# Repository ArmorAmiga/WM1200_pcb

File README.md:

# ArmorAmiga "Wishmaster" PCB repository

This is an early prototype of ARM-based A1200 turbo board.

PCB design was created in [KiCAD EDA](https://kicad.org/).

It consists of the following parts:
 * Wishmaster carrier board
 * Alinx AC7010/AC7020 Xilinx Zynq development board (available on Aliexpress, for example: https://aliexpress.ru/item/4000585279066.html). Most likely, you will also need a Xilinx JTAG cable to work with it as a developer.

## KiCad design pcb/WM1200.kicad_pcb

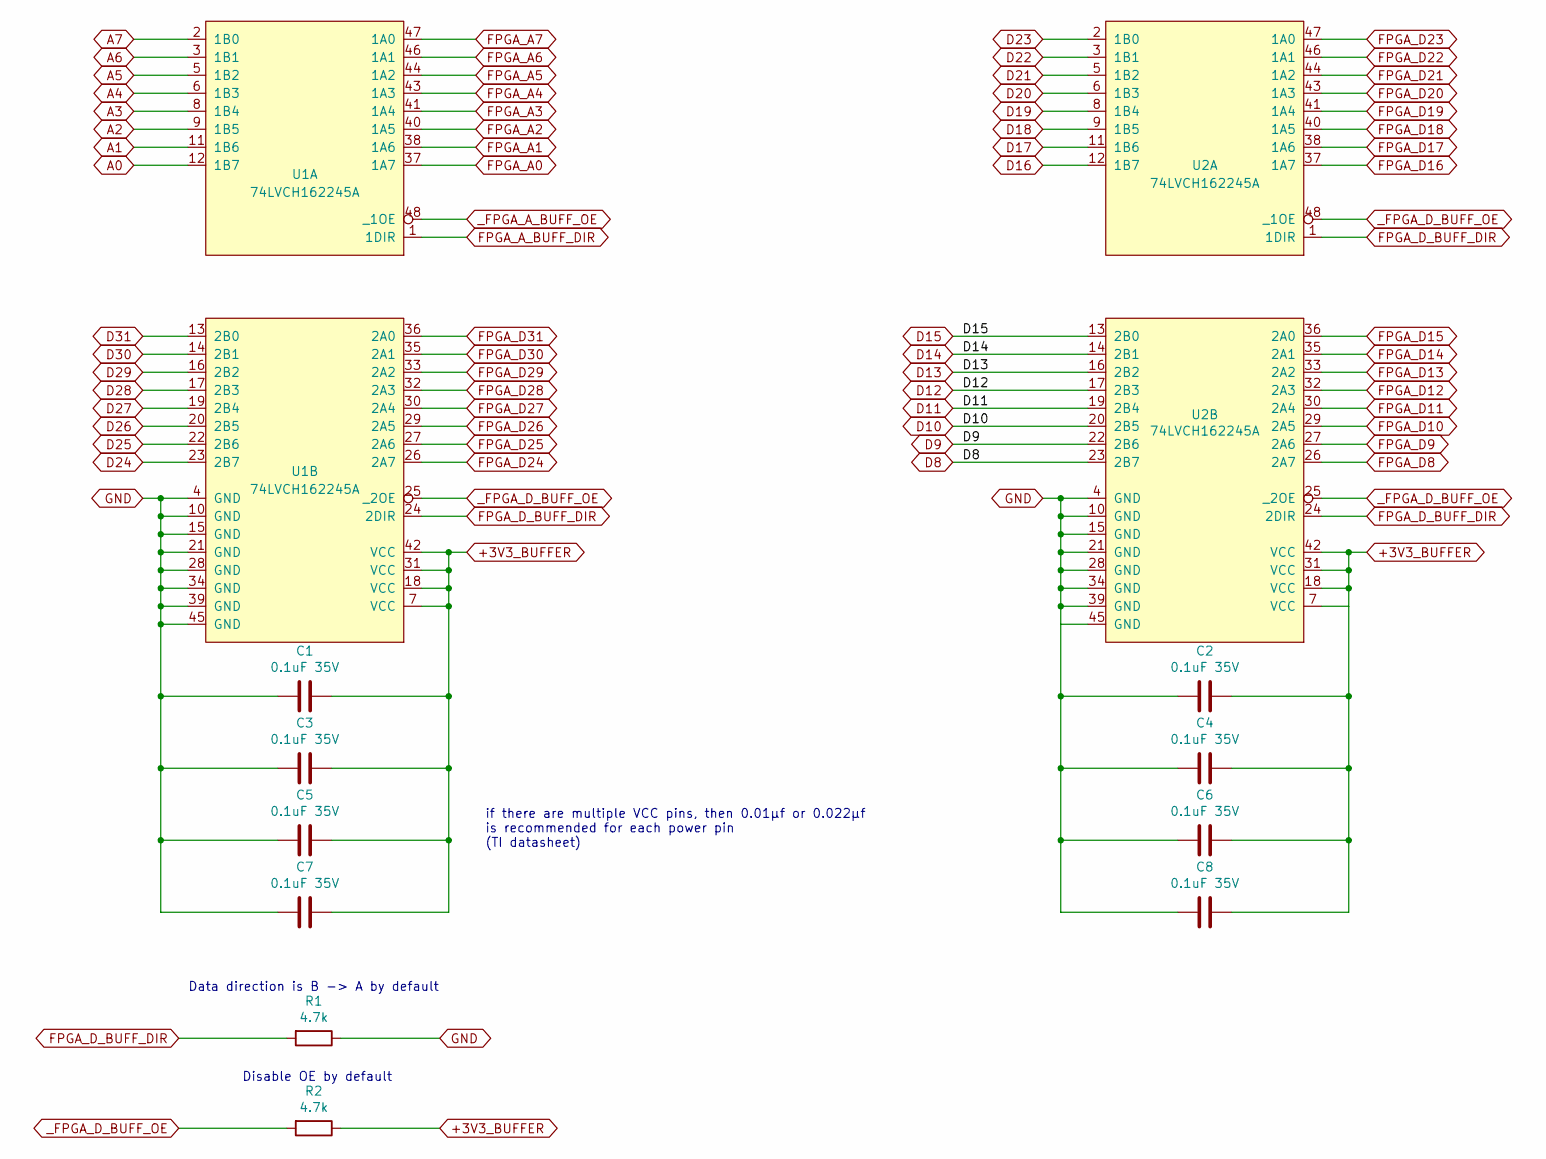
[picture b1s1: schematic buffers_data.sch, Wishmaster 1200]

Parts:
C1, C2, C3, C4, C5, C6, C7, C8: 0.1uF 35V; C_0402_1005Metric
R1, R2: 4.7k; R_0603_1608Metric_Pad1.05x0.95mm_HandSolder
U1, U2: 74LVCH162245A; TSSOP-48_6.1x12.5mm_P0.5mm

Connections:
+3V3_BUFFER: C1.2, C2.2, C3.2, C4.2, C5.2, C6.2, C7.2, C8.2, R2.1, U1.7 (VCC), U1.18 (VCC), U1.31 (VCC), U1.42 (VCC), U2.7 (VCC), U2.18 (VCC), U2.31 (VCC), U2.42 (VCC); also elsewhere on the board
A0: U1.12 (1B7); also elsewhere on the board
A1: U1.11 (1B6); also elsewhere on the board
A2: U1.9 (1B5); also elsewhere on the board
A3: U1.8 (1B4); also elsewhere on the board
A4: U1.6 (1B3); also elsewhere on the board
A5: U1.5 (1B2); also elsewhere on the board
A6: U1.3 (1B1); also elsewhere on the board
A7: U1.2 (1B0); also elsewhere on the board
D8: U2.23 (2B7); also elsewhere on the board
D9: U2.22 (2B6); also elsewhere on the board
D10: U2.20 (2B5); also elsewhere on the board
D11: U2.19 (2B4); also elsewhere on the board
D12: U2.17 (2B3); also elsewhere on the board
D13: U2.16 (2B2); also elsewhere on the board
D14: U2.14 (2B1); also elsewhere on the board
D15: U2.13 (2B0); also elsewhere on the board
D16: U2.12 (1B7); also elsewhere on the board
D17: U2.11 (1B6); also elsewhere on the board
D18: U2.9 (1B5); also elsewhere on the board
D19: U2.8 (1B4); also elsewhere on the board
D20: U2.6 (1B3); also elsewhere on the board
D21: U2.5 (1B2); also elsewhere on the board
D22: U2.3 (1B1); also elsewhere on the board
D23: U2.2 (1B0); also elsewhere on the board
D24: U1.23 (2B7); also elsewhere on the board
D25: U1.22 (2B6); also elsewhere on the board
D26: U1.20 (2B5); also elsewhere on the board
D27: U1.19 (2B4); also elsewhere on the board
D28: U1.17 (2B3); also elsewhere on the board
D29: U1.16 (2B2); also elsewhere on the board
D30: U1.14 (2B1); also elsewhere on the board
D31: U1.13 (2B0); also elsewhere on the board
FPGA_A0: U1.37 (1A7); also elsewhere on the board
FPGA_A1: U1.38 (1A6); also elsewhere on the board
FPGA_A2: U1.40 (1A5); also elsewhere on the board
FPGA_A3: U1.41 (1A4); also elsewhere on the board
FPGA_A4: U1.43 (1A3); also elsewhere on the board
FPGA_A5: U1.44 (1A2); also elsewhere on the board
FPGA_A6: U1.46 (1A1); also elsewhere on the board
FPGA_A7: U1.47 (1A0); also elsewhere on the board
FPGA_A_BUFF_DIR: U1.1 (1DIR); also elsewhere on the board
FPGA_D8: U2.26 (2A7); also elsewhere on the board
FPGA_D9: U2.27 (2A6); also elsewhere on the board
FPGA_D10: U2.29 (2A5); also elsewhere on the board
FPGA_D11: U2.30 (2A4); also elsewhere on the board
FPGA_D12: U2.32 (2A3); also elsewhere on the board
FPGA_D13: U2.33 (2A2); also elsewhere on the board
FPGA_D14: U2.35 (2A1); also elsewhere on the board
FPGA_D15: U2.36 (2A0); also elsewhere on the board
FPGA_D16: U2.37 (1A7); also elsewhere on the board
FPGA_D17: U2.38 (1A6); also elsewhere on the board
FPGA_D18: U2.40 (1A5); also elsewhere on the board
FPGA_D19: U2.41 (1A4); also elsewhere on the board
FPGA_D20: U2.43 (1A3); also elsewhere on the board
FPGA_D21: U2.44 (1A2); also elsewhere on the board
FPGA_D22: U2.46 (1A1); also elsewhere on the board
FPGA_D23: U2.47 (1A0); also elsewhere on the board
FPGA_D24: U1.26 (2A7); also elsewhere on the board
FPGA_D25: U1.27 (2A6); also elsewhere on the board
FPGA_D26: U1.29 (2A5); also elsewhere on the board
FPGA_D27: U1.30 (2A4); also elsewhere on the board
FPGA_D28: U1.32 (2A3); also elsewhere on the board
FPGA_D29: U1.33 (2A2); also elsewhere on the board
FPGA_D30: U1.35 (2A1); also elsewhere on the board
FPGA_D31: U1.36 (2A0); also elsewhere on the board
FPGA_D_BUFF_DIR: R1.2, U1.24 (2DIR), U2.1 (1DIR), U2.24 (2DIR); also elsewhere on the board
GND: C1.1, C2.1, C3.1, C4.1, C5.1, C6.1, C7.1, C8.1, R1.1, U1.4 (GND), U1.10 (GND), U1.15 (GND), U1.21 (GND), U1.28 (GND), U1.34 (GND), U1.39 (GND), U1.45 (GND), U2.4 (GND), U2.10 (GND), U2.15 (GND), U2.21 (GND), U2.28 (GND), U2.34 (GND), U2.39 (GND), U2.45 (GND); also elsewhere on the board
_FPGA_A_BUFF_OE: U1.48 (_1OE); also elsewhere on the board
_FPGA_D_BUFF_OE: R2.2, U1.25 (_2OE), U2.25 (_2OE), U2.48 (_1OE); also elsewhere on the board

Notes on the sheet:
Disable OE by default
Data direction is B -> A by default
if there are multiple VCC pins, then 0.01μf or 0.022μf is recommended for each power pin (TI datasheet)

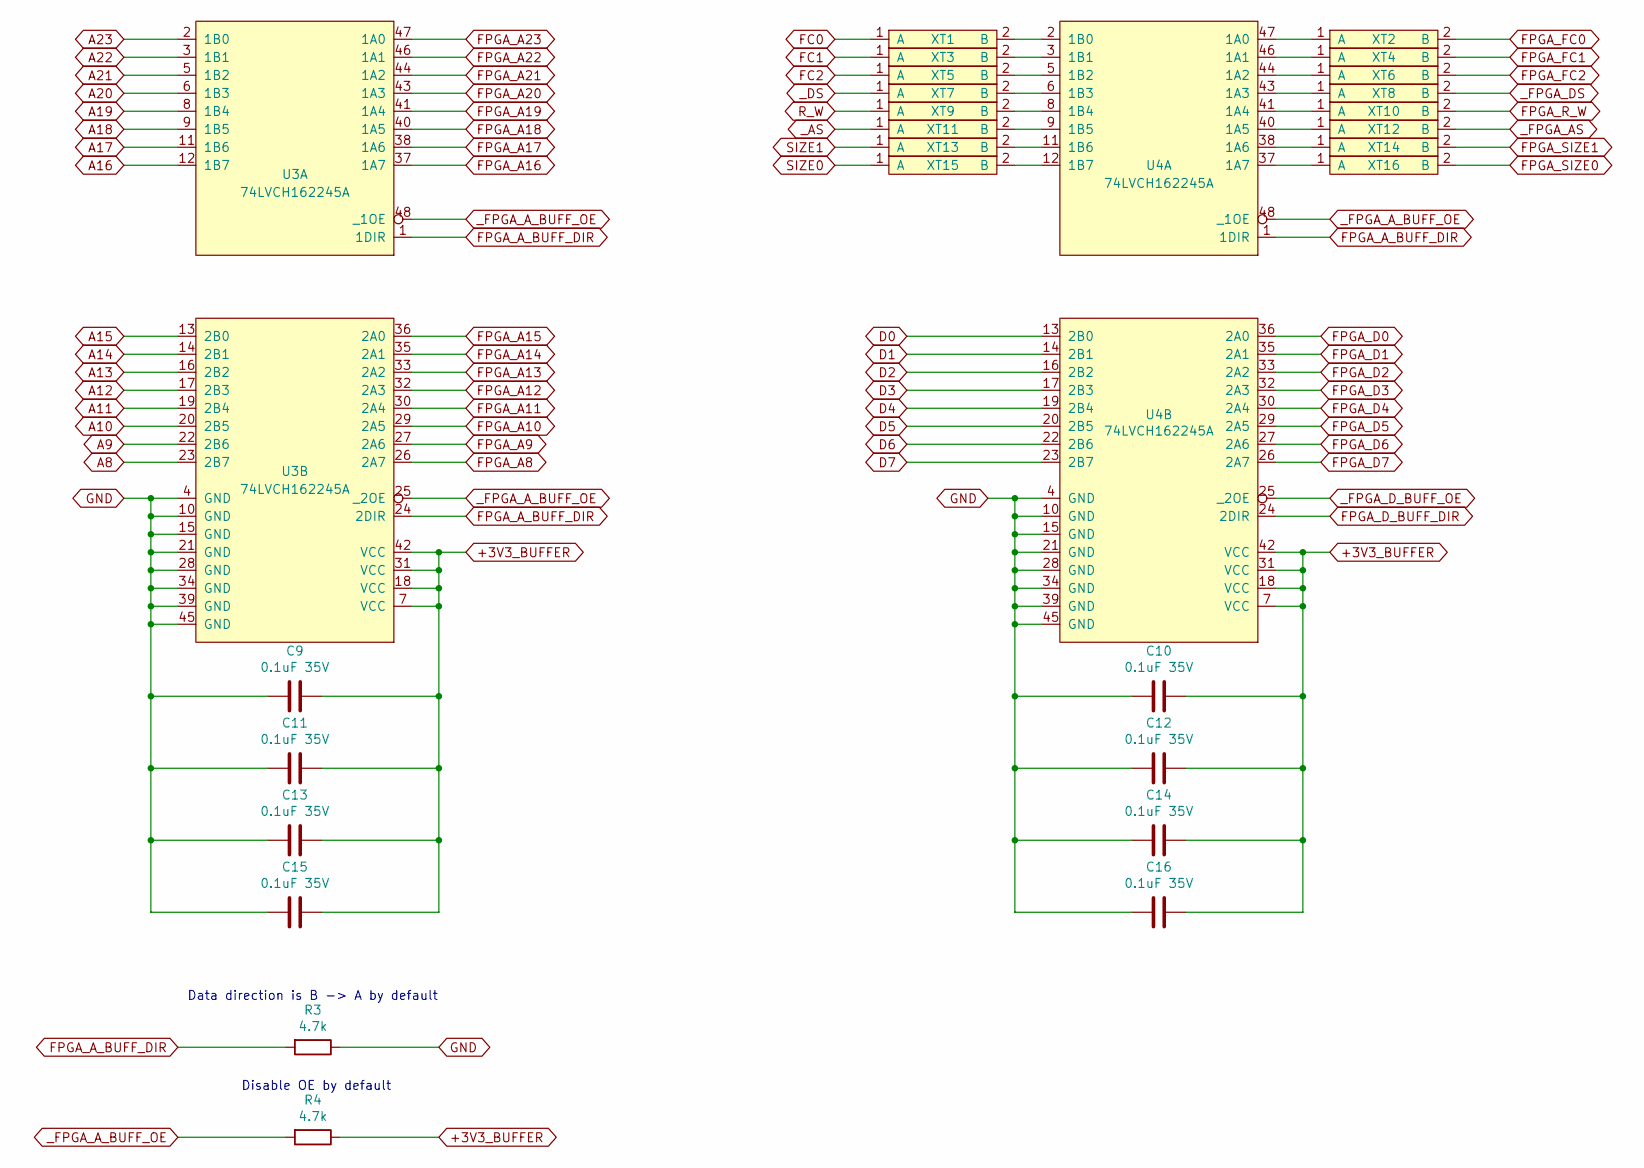
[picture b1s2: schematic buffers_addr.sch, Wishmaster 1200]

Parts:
C9, C10, C11, C12, C13, C14, C15, C16: 0.1uF 35V; C_0402_1005Metric
R3, R4: 4.7k; R_0603_1608Metric_Pad1.05x0.95mm_HandSolder
U3, U4: 74LVCH162245A; TSSOP-48_6.1x12.5mm_P0.5mm
XT1, XT2, XT3, XT4, XT5, XT6, XT7, XT8, XT9, XT10, XT11, XT12, XT13, XT14, XT15, XT16: testpoint_cutline

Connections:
+3V3_BUFFER: C9.2, C10.2, C11.2, C12.2, C13.2, C14.2, C15.2, C16.2, R4.1, U3.7 (VCC), U3.18 (VCC), U3.31 (VCC), U3.42 (VCC), U4.7 (VCC), U4.18 (VCC), U4.31 (VCC), U4.42 (VCC); also elsewhere on the board
A8: U3.23 (2B7); also elsewhere on the board
A9: U3.22 (2B6); also elsewhere on the board
A10: U3.20 (2B5); also elsewhere on the board
A11: U3.19 (2B4); also elsewhere on the board
A12: U3.17 (2B3); also elsewhere on the board
A13: U3.16 (2B2); also elsewhere on the board
A14: U3.14 (2B1); also elsewhere on the board
A15: U3.13 (2B0); also elsewhere on the board
A16: U3.12 (1B7); also elsewhere on the board
A17: U3.11 (1B6); also elsewhere on the board
A18: U3.9 (1B5); also elsewhere on the board
A19: U3.8 (1B4); also elsewhere on the board
A20: U3.6 (1B3); also elsewhere on the board
A21: U3.5 (1B2); also elsewhere on the board
A22: U3.3 (1B1); also elsewhere on the board
A23: U3.2 (1B0); also elsewhere on the board
D0: U4.13 (2B0); also elsewhere on the board
D1: U4.14 (2B1); also elsewhere on the board
D2: U4.16 (2B2); also elsewhere on the board
D3: U4.17 (2B3); also elsewhere on the board
D4: U4.19 (2B4); also elsewhere on the board
D5: U4.20 (2B5); also elsewhere on the board
D6: U4.22 (2B6); also elsewhere on the board
D7: U4.23 (2B7); also elsewhere on the board
FC0: XT1.1 (A); also elsewhere on the board
FC1: XT3.1 (A); also elsewhere on the board
FC2: XT5.1 (A); also elsewhere on the board
FPGA_A8: U3.26 (2A7); also elsewhere on the board
FPGA_A9: U3.27 (2A6); also elsewhere on the board
FPGA_A10: U3.29 (2A5); also elsewhere on the board
FPGA_A11: U3.30 (2A4); also elsewhere on the board
FPGA_A12: U3.32 (2A3); also elsewhere on the board
FPGA_A13: U3.33 (2A2); also elsewhere on the board
FPGA_A14: U3.35 (2A1); also elsewhere on the board
FPGA_A15: U3.36 (2A0); also elsewhere on the board
FPGA_A16: U3.37 (1A7); also elsewhere on the board
FPGA_A17: U3.38 (1A6); also elsewhere on the board
FPGA_A18: U3.40 (1A5); also elsewhere on the board
FPGA_A19: U3.41 (1A4); also elsewhere on the board
FPGA_A20: U3.43 (1A3); also elsewhere on the board
FPGA_A21: U3.44 (1A2); also elsewhere on the board
FPGA_A22: U3.46 (1A1); also elsewhere on the board
FPGA_A23: U3.47 (1A0); also elsewhere on the board
FPGA_A_BUFF_DIR: R3.2, U3.1 (1DIR), U3.24 (2DIR), U4.1 (1DIR); also elsewhere on the board
FPGA_D0: U4.36 (2A0); also elsewhere on the board
FPGA_D1: U4.35 (2A1); also elsewhere on the board
FPGA_D2: U4.33 (2A2); also elsewhere on the board
FPGA_D3: U4.32 (2A3); also elsewhere on the board
FPGA_D4: U4.30 (2A4); also elsewhere on the board
FPGA_D5: U4.29 (2A5); also elsewhere on the board
FPGA_D6: U4.27 (2A6); also elsewhere on the board
FPGA_D7: U4.26 (2A7); also elsewhere on the board
FPGA_D_BUFF_DIR: U4.24 (2DIR); also elsewhere on the board
FPGA_FC0: XT2.2 (B); also elsewhere on the board
FPGA_FC1: XT4.2 (B); also elsewhere on the board
FPGA_FC2: XT6.2 (B); also elsewhere on the board
FPGA_R_W: XT10.2 (B); also elsewhere on the board
FPGA_SIZE0: XT16.2 (B); also elsewhere on the board
FPGA_SIZE1: XT14.2 (B); also elsewhere on the board
GND: C9.1, C10.1, C11.1, C12.1, C13.1, C14.1, C15.1, C16.1, R3.1, U3.4 (GND), U3.10 (GND), U3.15 (GND), U3.21 (GND), U3.28 (GND), U3.34 (GND), U3.39 (GND), U3.45 (GND), U4.4 (GND), U4.10 (GND), U4.15 (GND), U4.21 (GND), U4.28 (GND), U4.34 (GND), U4.39 (GND), U4.45 (GND); also elsewhere on the board
unnamed: U4.2 (1B0), XT1.2 (B)
unnamed: U4.3 (1B1), XT3.2 (B)
unnamed: U4.5 (1B2), XT5.2 (B)
unnamed: U4.6 (1B3), XT7.2 (B)
unnamed: U4.8 (1B4), XT9.2 (B)
unnamed: U4.9 (1B5), XT11.2 (B)
unnamed: U4.11 (1B6), XT13.2 (B)
unnamed: U4.12 (1B7), XT15.2 (B)
unnamed: U4.37 (1A7), XT16.1 (A)
unnamed: U4.38 (1A6), XT14.1 (A)
unnamed: U4.40 (1A5), XT12.1 (A)
unnamed: U4.41 (1A4), XT10.1 (A)
unnamed: U4.43 (1A3), XT8.1 (A)
unnamed: U4.44 (1A2), XT6.1 (A)
unnamed: U4.46 (1A1), XT4.1 (A)
unnamed: U4.47 (1A0), XT2.1 (A)
R_W: XT9.1 (A); also elsewhere on the board
SIZE0: XT15.1 (A); also elsewhere on the board
SIZE1: XT13.1 (A); also elsewhere on the board
_AS: XT11.1 (A); also elsewhere on the board
_DS: XT7.1 (A); also elsewhere on the board
_FPGA_AS: XT12.2 (B); also elsewhere on the board
_FPGA_A_BUFF_OE: R4.2, U3.25 (_2OE), U3.48 (_1OE), U4.48 (_1OE); also elsewhere on the board
_FPGA_DS: XT8.2 (B); also elsewhere on the board
_FPGA_D_BUFF_OE: U4.25 (_2OE); also elsewhere on the board

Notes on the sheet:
Disable OE by default
Data direction is B -> A by default

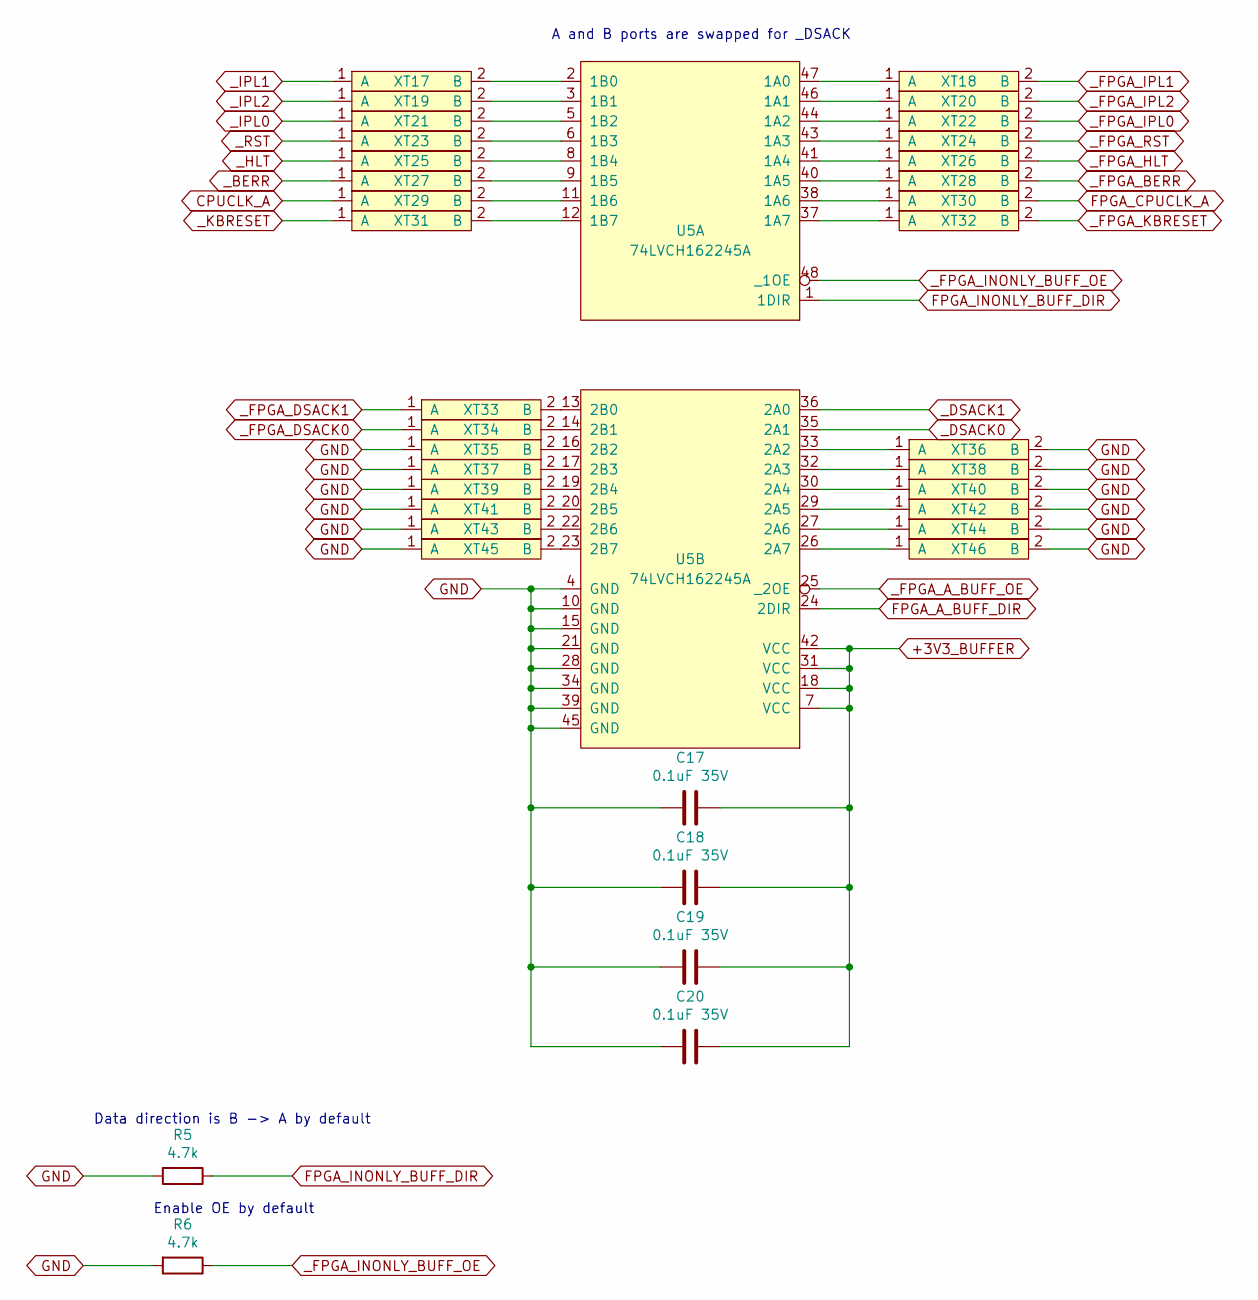
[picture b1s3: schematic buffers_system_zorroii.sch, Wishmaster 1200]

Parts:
C17, C18, C19, C20: 0.1uF 35V; C_0402_1005Metric
R5, R6: 4.7k; R_0603_1608Metric_Pad1.05x0.95mm_HandSolder
U5: 74LVCH162245A; TSSOP-48_6.1x12.5mm_P0.5mm
XT17, XT18, XT19, XT20, XT21, XT22, XT23, XT24, XT25, XT26, XT27, XT28, XT29, XT30, XT31, XT32, XT33, XT34, XT35, XT36, XT37, XT38, XT39, XT40, XT41, XT42, XT43, XT44, XT45, XT46: testpoint_cutline

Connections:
+3V3_BUFFER: C17.2, C18.2, C19.2, C20.2, U5.7 (VCC), U5.18 (VCC), U5.31 (VCC), U5.42 (VCC); also elsewhere on the board
CPUCLK_A: XT29.1 (A); also elsewhere on the board
FPGA_A_BUFF_DIR: U5.24 (2DIR); also elsewhere on the board
FPGA_CPUCLK_A: XT30.2 (B); also elsewhere on the board
FPGA_INONLY_BUFF_DIR: R5.1, U5.1 (1DIR)
GND: C17.1, C18.1, C19.1, C20.1, R5.2, R6.2, U5.4 (GND), U5.10 (GND), U5.15 (GND), U5.21 (GND), U5.28 (GND), U5.34 (GND), U5.39 (GND), U5.45 (GND), XT35.1 (A), XT36.2 (B), XT37.1 (A), XT38.2 (B), XT39.1 (A), XT40.2 (B), XT41.1 (A), XT42.2 (B), XT43.1 (A), XT44.2 (B), XT45.1 (A), XT46.2 (B); also elsewhere on the board
unnamed: U5.2 (1B0), XT17.2 (B)
unnamed: U5.3 (1B1), XT19.2 (B)
unnamed: U5.5 (1B2), XT21.2 (B)
unnamed: U5.6 (1B3), XT23.2 (B)
unnamed: U5.8 (1B4), XT25.2 (B)
unnamed: U5.9 (1B5), XT27.2 (B)
unnamed: U5.11 (1B6), XT29.2 (B)
unnamed: U5.12 (1B7), XT31.2 (B)
unnamed: U5.13 (2B0), XT33.2 (B)
unnamed: U5.14 (2B1), XT34.2 (B)
unnamed: U5.16 (2B2), XT35.2 (B)
unnamed: U5.17 (2B3), XT37.2 (B)
unnamed: U5.19 (2B4), XT39.2 (B)
unnamed: U5.20 (2B5), XT41.2 (B)
unnamed: U5.22 (2B6), XT43.2 (B)
unnamed: U5.23 (2B7), XT45.2 (B)
unnamed: U5.26 (2A7), XT46.1 (A)
unnamed: U5.27 (2A6), XT44.1 (A)
unnamed: U5.29 (2A5), XT42.1 (A)
unnamed: U5.30 (2A4), XT40.1 (A)
unnamed: U5.32 (2A3), XT38.1 (A)
unnamed: U5.33 (2A2), XT36.1 (A)
unnamed: U5.37 (1A7), XT32.1 (A)
unnamed: U5.38 (1A6), XT30.1 (A)
unnamed: U5.40 (1A5), XT28.1 (A)
unnamed: U5.41 (1A4), XT26.1 (A)
unnamed: U5.43 (1A3), XT24.1 (A)
unnamed: U5.44 (1A2), XT22.1 (A)
unnamed: U5.46 (1A1), XT20.1 (A)
unnamed: U5.47 (1A0), XT18.1 (A)
_BERR: XT27.1 (A); also elsewhere on the board
_DSACK0: U5.35 (2A1); also elsewhere on the board
_DSACK1: U5.36 (2A0); also elsewhere on the board
_FPGA_A_BUFF_OE: U5.25 (_2OE); also elsewhere on the board
_FPGA_BERR: XT28.2 (B); also elsewhere on the board
_FPGA_DSACK0: XT34.1 (A); also elsewhere on the board
_FPGA_DSACK1: XT33.1 (A); also elsewhere on the board
_FPGA_HLT: XT26.2 (B); also elsewhere on the board
_FPGA_INONLY_BUFF_OE: R6.1, U5.48 (_1OE)
_FPGA_IPL0: XT22.2 (B); also elsewhere on the board
_FPGA_IPL1: XT18.2 (B); also elsewhere on the board
_FPGA_IPL2: XT20.2 (B); also elsewhere on the board
_FPGA_KBRESET: XT32.2 (B); also elsewhere on the board
_FPGA_RST: XT24.2 (B); also elsewhere on the board
_HLT: XT25.1 (A); also elsewhere on the board
_IPL0: XT21.1 (A); also elsewhere on the board
_IPL1: XT17.1 (A); also elsewhere on the board
_IPL2: XT19.1 (A); also elsewhere on the board
_KBRESET: XT31.1 (A); also elsewhere on the board
_RST: XT23.1 (A); also elsewhere on the board

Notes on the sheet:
Enable OE by default
Data direction is B -> A by default
A and B ports are swapped for _DSACK

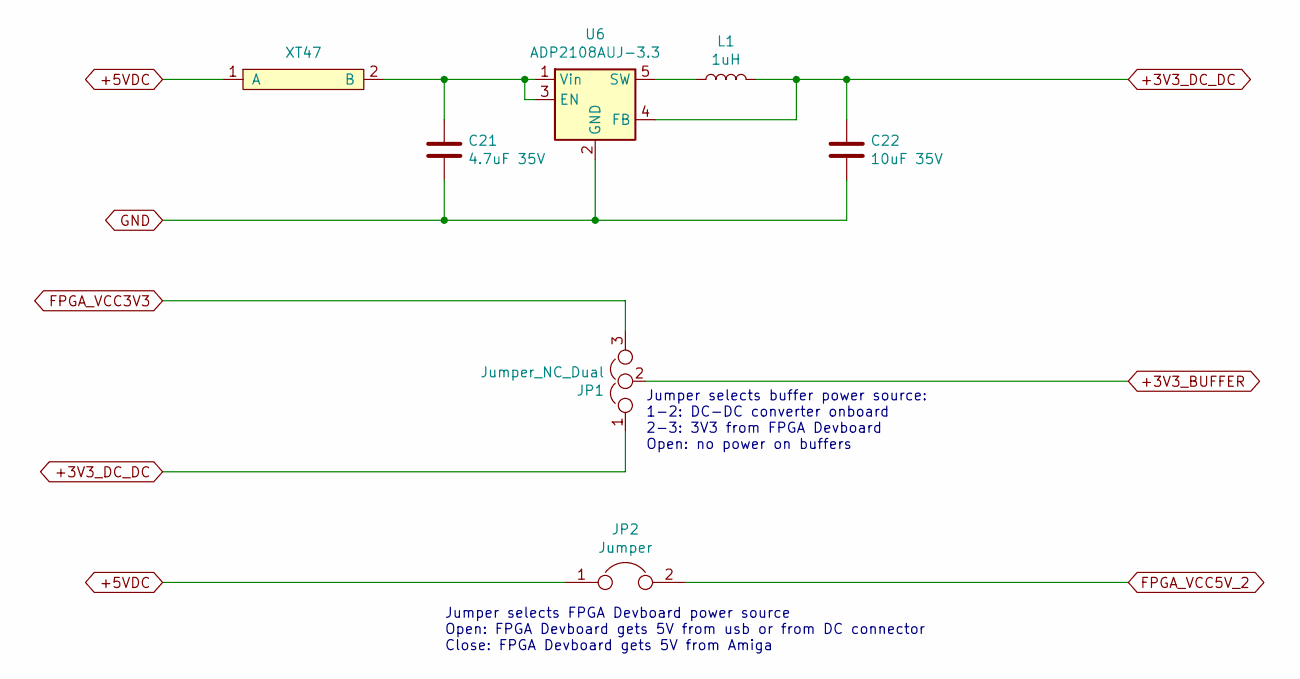
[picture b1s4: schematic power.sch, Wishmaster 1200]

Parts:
C21: 4.7uF 35V; C_1210_3225Metric_Pad1.42x2.65mm_HandSolder
C22: 10uF 35V; C_1210_3225Metric_Pad1.42x2.65mm_HandSolder
JP1: Jumper_NC_Dual; PinHeader_1x03_P2.54mm_Vertical
JP2: Jumper; PinHeader_1x02_P2.54mm_Vertical
L1: 1uH; L_0603_1608Metric_Pad1.05x0.95mm_HandSolder
U6: ADP2108AUJ-3.3; TSOT-23-5
XT47: testpoint_cutline; testpoint_cutline_fat

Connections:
+3V3_BUFFER: JP1.2; also elsewhere on the board
+3V3_DC_DC: C22.1, JP1.1, L1.2, U6.4 (FB)
+5VDC: JP2.1, XT47.1 (A); also elsewhere on the board
FPGA_VCC3V3: JP1.3; also elsewhere on the board
FPGA_VCC5V_2: JP2.2; also elsewhere on the board
GND: C21.2, C22.2, U6.2 (GND); also elsewhere on the board
unnamed: C21.1, U6.1 (Vin), U6.3 (EN), XT47.2 (B)
unnamed: L1.1, U6.5 (SW)

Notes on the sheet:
Jumper selects buffer power source: 1-2: DC-DC converter onboard 2-3: 3V3 from FPGA Devboard Open: no power on buffers
Jumper selects FPGA Devboard power source Open: FPGA Devboard gets 5V from usb or from DC connector Close: FPGA Devboard gets 5V from Amiga

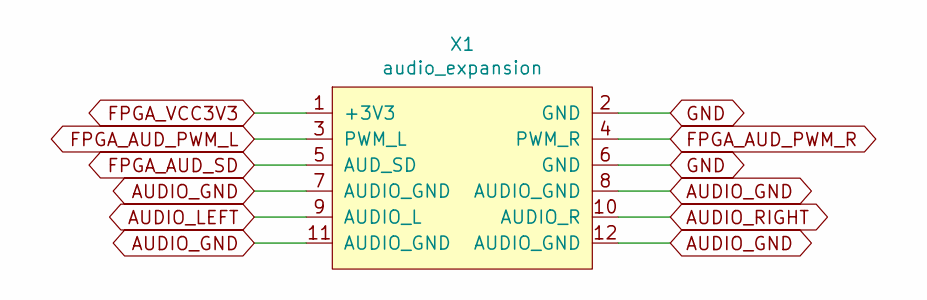
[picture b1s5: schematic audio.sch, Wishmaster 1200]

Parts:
X1: audio_expansion; PinHeader_2x06_P2.54mm_Vertical

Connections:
AUDIO_GND: X1.7 (AUDIO_GND), X1.8 (AUDIO_GND), X1.11 (AUDIO_GND), X1.12 (AUDIO_GND); also elsewhere on the board
AUDIO_LEFT: X1.9 (AUDIO_L); also elsewhere on the board
AUDIO_RIGHT: X1.10 (AUDIO_R); also elsewhere on the board
FPGA_AUD_PWM_L: X1.3 (PWM_L); also elsewhere on the board
FPGA_AUD_PWM_R: X1.4 (PWM_R); also elsewhere on the board
FPGA_AUD_SD: X1.5 (AUD_SD); also elsewhere on the board
FPGA_VCC3V3: X1.1 (+3V3); also elsewhere on the board
GND: X1.2 (GND), X1.6 (GND); also elsewhere on the board

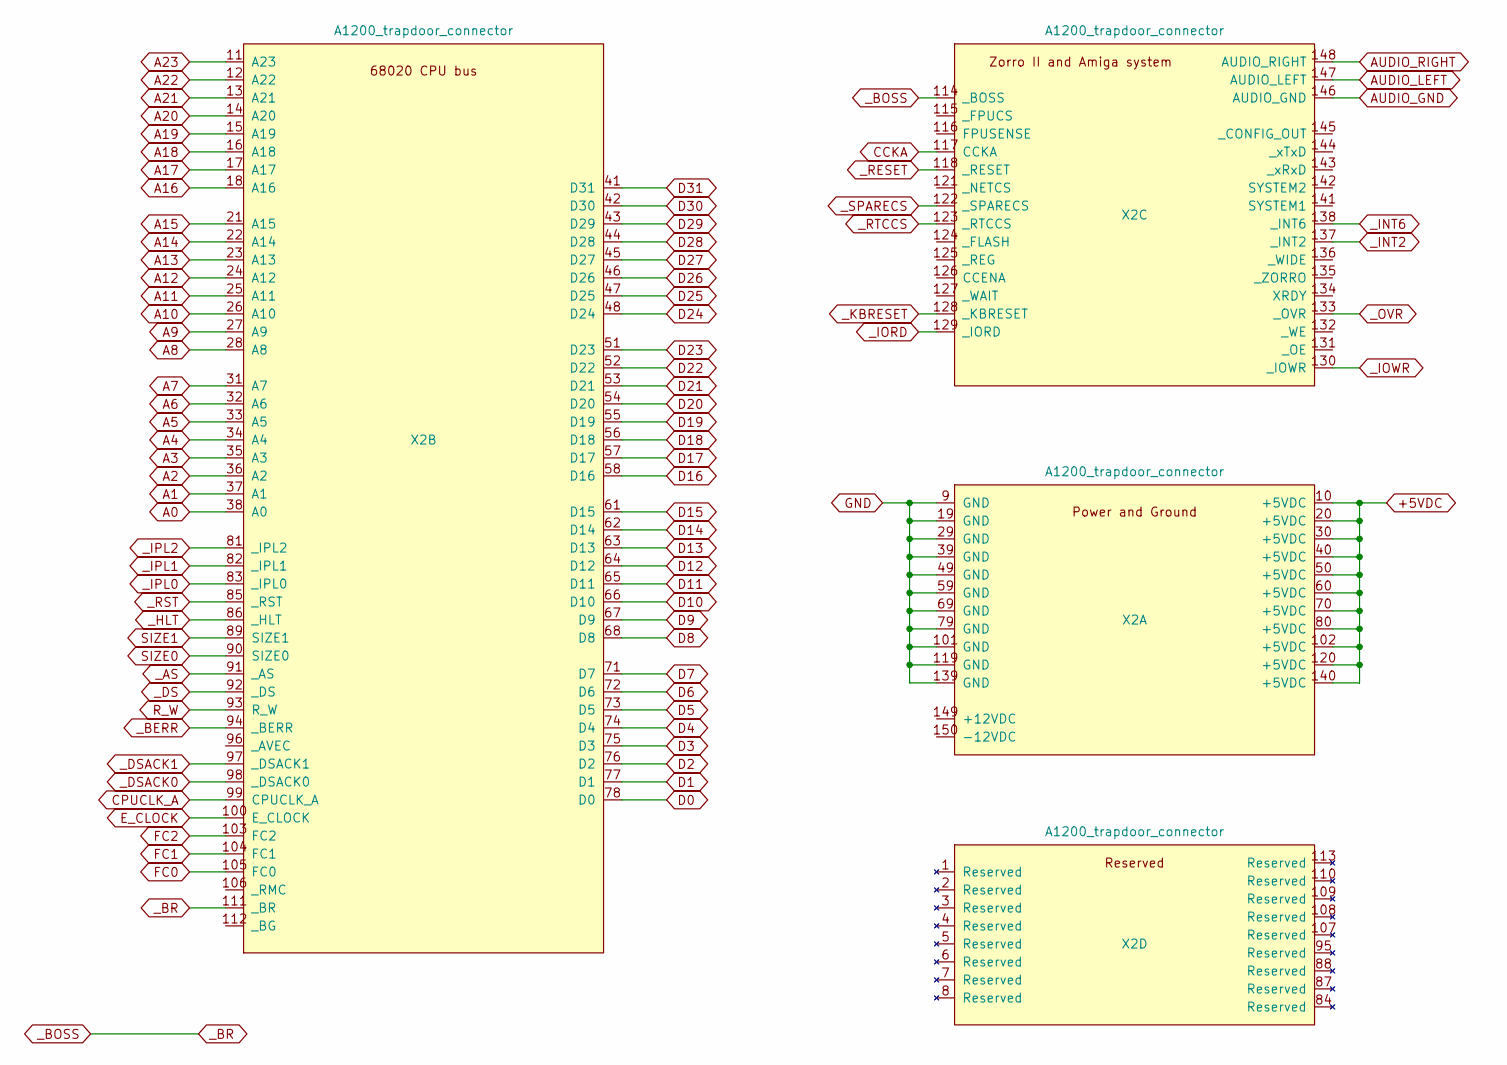
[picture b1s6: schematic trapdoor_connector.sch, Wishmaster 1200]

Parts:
X2: A1200_trapdoor_connector; Trapdoor_connector

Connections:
+5VDC: X2.10 (+5VDC), X2.20 (+5VDC), X2.30 (+5VDC), X2.40 (+5VDC), X2.50 (+5VDC), X2.60 (+5VDC), X2.70 (+5VDC), X2.80 (+5VDC), X2.102 (+5VDC), X2.120 (+5VDC), X2.140 (+5VDC); also elsewhere on the board
A0: X2.38 (A0); also elsewhere on the board
A1: X2.37 (A1); also elsewhere on the board
A2: X2.36 (A2); also elsewhere on the board
A3: X2.35 (A3); also elsewhere on the board
A4: X2.34 (A4); also elsewhere on the board
A5: X2.33 (A5); also elsewhere on the board
A6: X2.32 (A6); also elsewhere on the board
A7: X2.31 (A7); also elsewhere on the board
A8: X2.28 (A8); also elsewhere on the board
A9: X2.27 (A9); also elsewhere on the board
A10: X2.26 (A10); also elsewhere on the board
A11: X2.25 (A11); also elsewhere on the board
A12: X2.24 (A12); also elsewhere on the board
A13: X2.23 (A13); also elsewhere on the board
A14: X2.22 (A14); also elsewhere on the board
A15: X2.21 (A15); also elsewhere on the board
A16: X2.18 (A16); also elsewhere on the board
A17: X2.17 (A17); also elsewhere on the board
A18: X2.16 (A18); also elsewhere on the board
A19: X2.15 (A19); also elsewhere on the board
A20: X2.14 (A20); also elsewhere on the board
A21: X2.13 (A21); also elsewhere on the board
A22: X2.12 (A22); also elsewhere on the board
A23: X2.11 (A23); also elsewhere on the board
AUDIO_GND: X2.146 (AUDIO_GND); also elsewhere on the board
AUDIO_LEFT: X2.147 (AUDIO_LEFT); also elsewhere on the board
AUDIO_RIGHT: X2.148 (AUDIO_RIGHT); also elsewhere on the board
CCKA: X2.117 (CCKA)
CPUCLK_A: X2.99 (CPUCLK_A); also elsewhere on the board
D0: X2.78 (D0); also elsewhere on the board
D1: X2.77 (D1); also elsewhere on the board
D2: X2.76 (D2); also elsewhere on the board
D3: X2.75 (D3); also elsewhere on the board
D4: X2.74 (D4); also elsewhere on the board
D5: X2.73 (D5); also elsewhere on the board
D6: X2.72 (D6); also elsewhere on the board
D7: X2.71 (D7); also elsewhere on the board
D8: X2.68 (D8); also elsewhere on the board
D9: X2.67 (D9); also elsewhere on the board
D10: X2.66 (D10); also elsewhere on the board
D11: X2.65 (D11); also elsewhere on the board
D12: X2.64 (D12); also elsewhere on the board
D13: X2.63 (D13); also elsewhere on the board
D14: X2.62 (D14); also elsewhere on the board
D15: X2.61 (D15); also elsewhere on the board
D16: X2.58 (D16); also elsewhere on the board
D17: X2.57 (D17); also elsewhere on the board
D18: X2.56 (D18); also elsewhere on the board
D19: X2.55 (D19); also elsewhere on the board
D20: X2.54 (D20); also elsewhere on the board
D21: X2.53 (D21); also elsewhere on the board
D22: X2.52 (D22); also elsewhere on the board
D23: X2.51 (D23); also elsewhere on the board
D24: X2.48 (D24); also elsewhere on the board
D25: X2.47 (D25); also elsewhere on the board
D26: X2.46 (D26); also elsewhere on the board
D27: X2.45 (D27); also elsewhere on the board
D28: X2.44 (D28); also elsewhere on the board
D29: X2.43 (D29); also elsewhere on the board
D30: X2.42 (D30); also elsewhere on the board
D31: X2.41 (D31); also elsewhere on the board
E_CLOCK: X2.100 (E_CLOCK)
FC0: X2.105 (FC0); also elsewhere on the board
FC1: X2.104 (FC1); also elsewhere on the board
FC2: X2.103 (FC2); also elsewhere on the board
GND: X2.9 (GND), X2.19 (GND), X2.29 (GND), X2.39 (GND), X2.49 (GND), X2.59 (GND), X2.69 (GND), X2.79 (GND), X2.101 (GND), X2.119 (GND), X2.139 (GND); also elsewhere on the board
R_W: X2.93 (R_W); also elsewhere on the board
SIZE0: X2.90 (SIZE0); also elsewhere on the board
SIZE1: X2.89 (SIZE1); also elsewhere on the board
_AS: X2.91 (_AS); also elsewhere on the board
_BERR: X2.94 (_BERR); also elsewhere on the board
_BOSS: X2.111 (_BR), X2.114 (_BOSS); also elsewhere on the board
_DS: X2.92 (_DS); also elsewhere on the board
_DSACK0: X2.98 (_DSACK0); also elsewhere on the board
_DSACK1: X2.97 (_DSACK1); also elsewhere on the board
_HLT: X2.86 (_HLT); also elsewhere on the board
_INT2: X2.137 (_INT2); also elsewhere on the board
_INT6: X2.138 (_INT6); also elsewhere on the board
_IORD: X2.129 (_IORD)
_IOWR: X2.130 (_IOWR)
_IPL0: X2.83 (_IPL0); also elsewhere on the board
_IPL1: X2.82 (_IPL1); also elsewhere on the board
_IPL2: X2.81 (_IPL2); also elsewhere on the board
_KBRESET: X2.128 (_KBRESET); also elsewhere on the board
_OVR: X2.133 (_OVR); also elsewhere on the board
_RESET: X2.118 (_RESET)
_RST: X2.85 (_RST); also elsewhere on the board
_RTCCS: X2.123 (_RTCCS)
_SPARECS: X2.122 (_SPARECS)

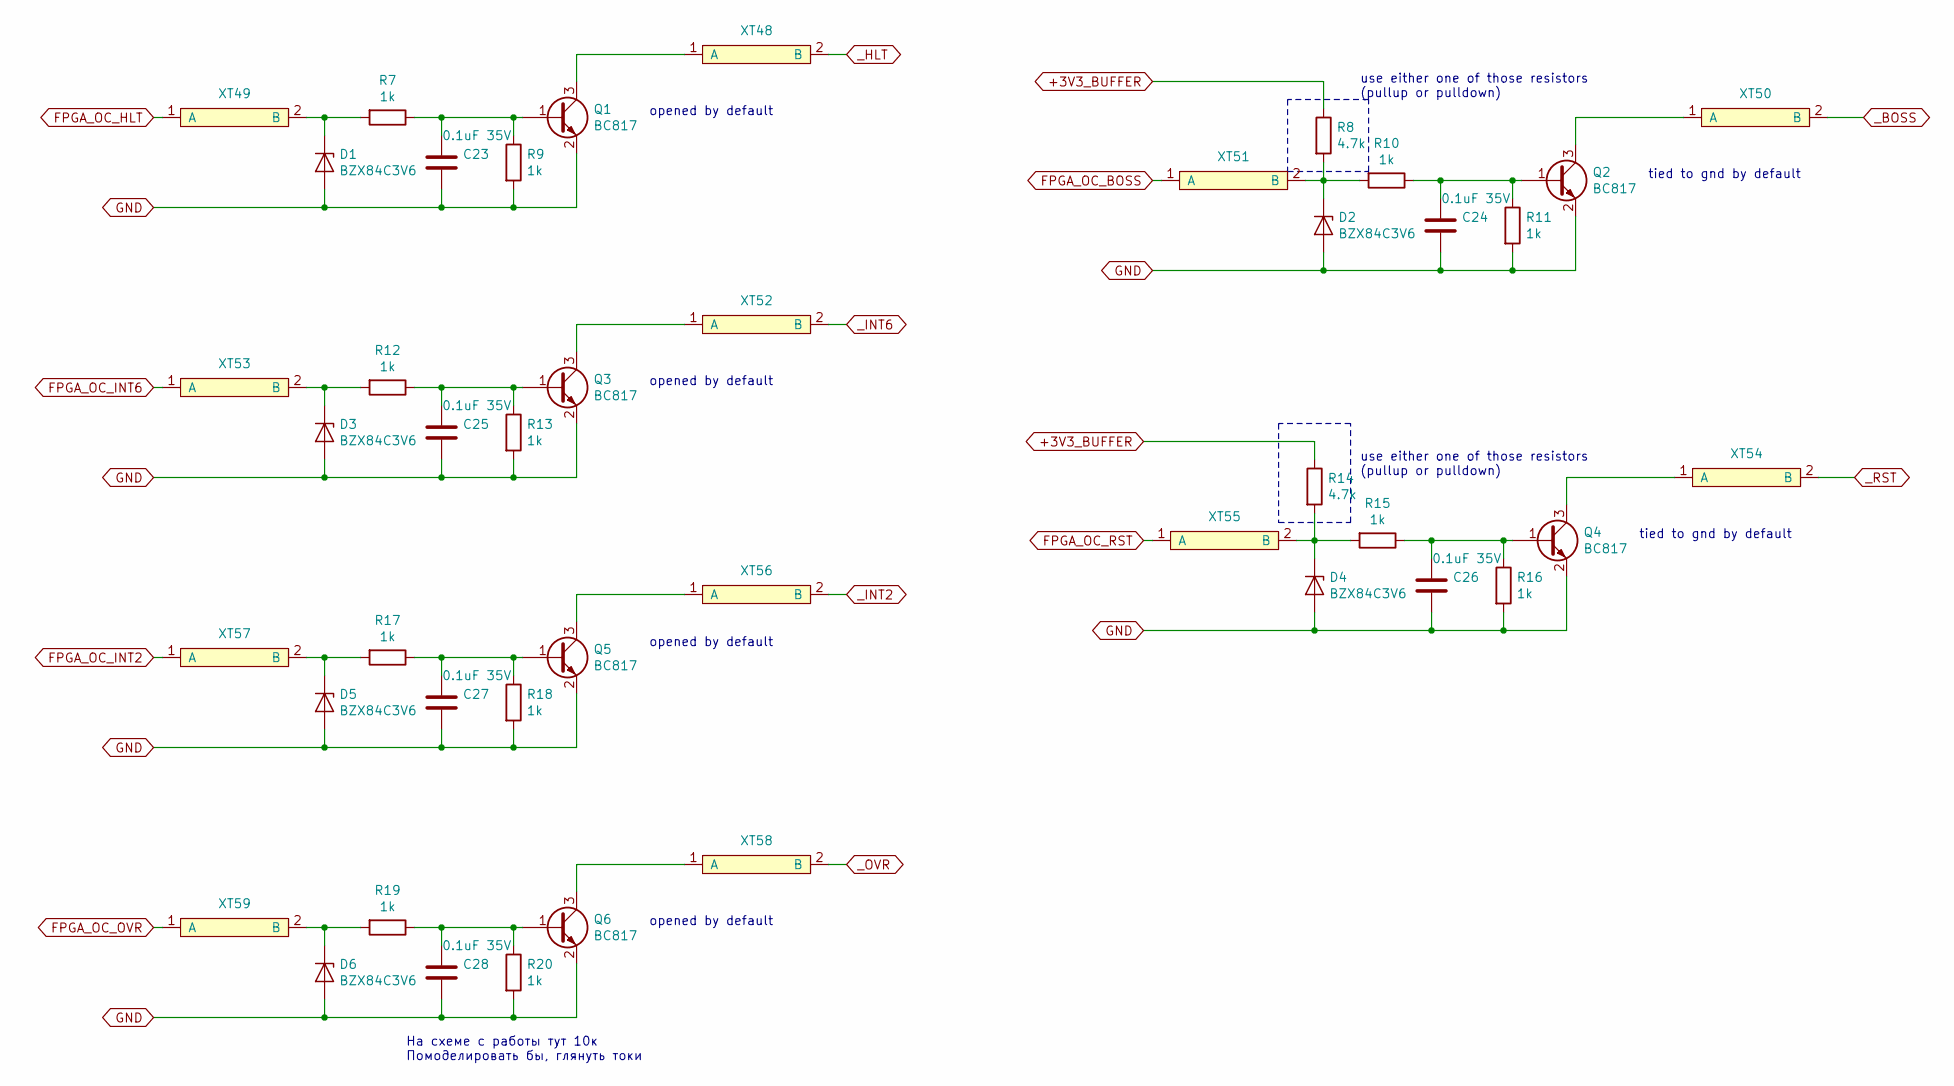
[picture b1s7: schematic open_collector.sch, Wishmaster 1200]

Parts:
C23, C24, C25, C26, C27, C28: 0.1uF 35V; C_0603_1608Metric_Pad1.05x0.95mm_HandSolder
D1, D2, D3, D4, D5, D6: BZX84C3V6; D_SOT-23_ANK
Q1, Q2, Q3, Q4, Q5, Q6: BC817; SOT-23
R7, R9, R10, R11, R12, R13, R15, R16, R17, R18, R19, R20: 1k; R_0603_1608Metric_Pad1.05x0.95mm_HandSolder
R8, R14: 4.7k; R_0603_1608Metric_Pad1.05x0.95mm_HandSolder
XT48, XT49, XT50, XT51, XT52, XT53, XT54, XT55, XT56, XT57, XT58, XT59: testpoint_cutline

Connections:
+3V3_BUFFER: R8.1, R14.1; also elsewhere on the board
FPGA_OC_BOSS: XT51.1 (A); also elsewhere on the board
FPGA_OC_HLT: XT49.1 (A); also elsewhere on the board
FPGA_OC_INT2: XT57.1 (A); also elsewhere on the board
FPGA_OC_INT6: XT53.1 (A); also elsewhere on the board
FPGA_OC_OVR: XT59.1 (A); also elsewhere on the board
FPGA_OC_RST: XT55.1 (A); also elsewhere on the board
GND: C23.1, C24.1, C25.1, C26.1, C27.1, C28.1, D1.2 (A), D2.2 (A), D3.2 (A), D4.2 (A), D5.2 (A), D6.2 (A), Q1.2 (E), Q2.2 (E), Q3.2 (E), Q4.2 (E), Q5.2 (E), Q6.2 (E), R9.2, R11.2, R13.2, R16.2, R18.2, R20.2; also elsewhere on the board
unnamed: C23.2, Q1.1 (B), R7.1, R9.1
unnamed: C24.2, Q2.1 (B), R10.1, R11.1
unnamed: C25.2, Q3.1 (B), R12.1, R13.1
unnamed: C26.2, Q4.1 (B), R15.1, R16.1
unnamed: C27.2, Q5.1 (B), R17.1, R18.1
unnamed: C28.2, Q6.1 (B), R19.1, R20.1
unnamed: D1.1 (K), R7.2, XT49.2 (B)
unnamed: D2.1 (K), R8.2, R10.2, XT51.2 (B)
unnamed: D3.1 (K), R12.2, XT53.2 (B)
unnamed: D4.1 (K), R14.2, R15.2, XT55.2 (B)
unnamed: D5.1 (K), R17.2, XT57.2 (B)
unnamed: D6.1 (K), R19.2, XT59.2 (B)
unnamed: Q1.3 (C), XT48.1 (A)
unnamed: Q2.3 (C), XT50.1 (A)
unnamed: Q3.3 (C), XT52.1 (A)
unnamed: Q4.3 (C), XT54.1 (A)
unnamed: Q5.3 (C), XT56.1 (A)
unnamed: Q6.3 (C), XT58.1 (A)
_BOSS: XT50.2 (B); also elsewhere on the board
_HLT: XT48.2 (B); also elsewhere on the board
_INT2: XT56.2 (B); also elsewhere on the board
_INT6: XT52.2 (B); also elsewhere on the board
_OVR: XT58.2 (B); also elsewhere on the board
_RST: XT54.2 (B); also elsewhere on the board

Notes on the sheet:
opened by default
tied to gnd by default
use either one of those resistors (pullup or pulldown)
На схеме с работы тут 10к Помоделировать бы, глянуть токи
